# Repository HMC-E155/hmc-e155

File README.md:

# E155: Microprocessor-based Systems at Harvey Mudd College

This repository contains source code related to E155: Microprocessor-based Systems (MicroPs) at Harvey Mudd College.
See the [course website](https://hmc-e155.github.io/) for more details.

# Repository Structure

- [board](./board/) contains KiCad design files for the motherboard and breadboard adapter.
- [lab](./lab/) contains starter code for the labs as applicable.

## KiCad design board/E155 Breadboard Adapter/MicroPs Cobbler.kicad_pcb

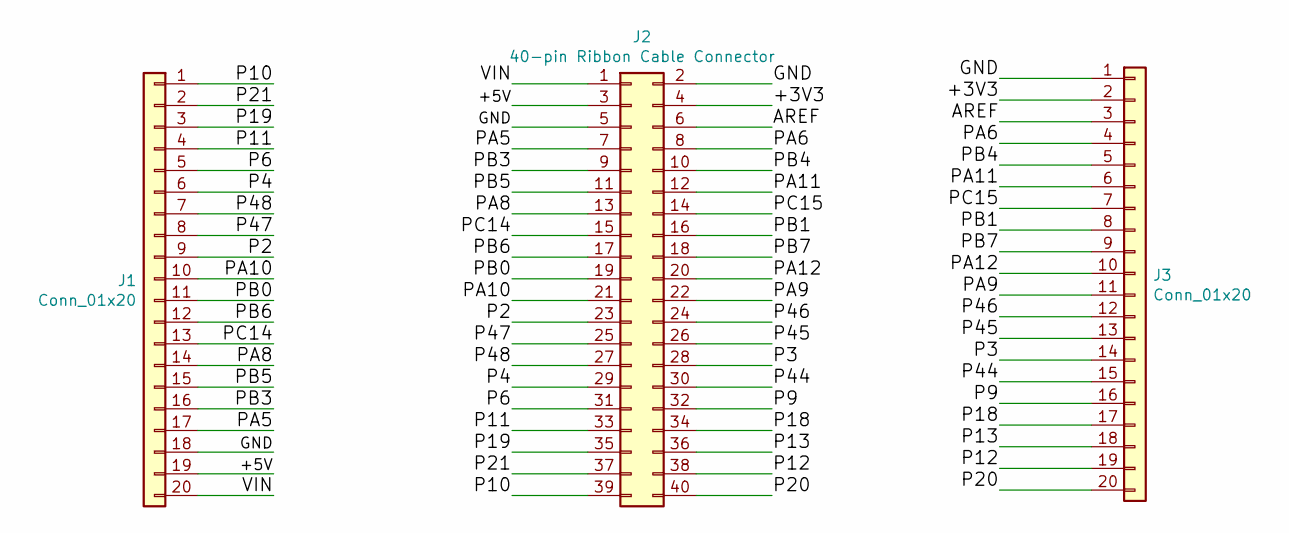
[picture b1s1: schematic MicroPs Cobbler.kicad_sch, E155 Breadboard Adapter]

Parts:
J1, J3: Conn_01x20; PinHeader_1x20_P2.54mm_Vertical
J2: 40-pin Ribbon Cable Connector; 2x20 Pin Header Keyed

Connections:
/+3V3: J2.4, J3.2
/+5V: J1.19, J2.3
/AREF: J2.6, J3.3
/GND: J1.18, J2.2, J2.5, J3.1
/P2: J1.9, J2.23
/P3: J2.28, J3.14
/P4: J1.6, J2.29
/P6: J1.5, J2.31
/P9: J2.32, J3.16
/P10: J1.1, J2.39
/P11: J1.4, J2.33
/P12: J2.38, J3.19
/P13: J2.36, J3.18
/P18: J2.34, J3.17
/P19: J1.3, J2.35
/P20: J2.40, J3.20
/P21: J1.2, J2.37
/P44: J2.30, J3.15
/P45: J2.26, J3.13
/P46: J2.24, J3.12
/P47: J1.8, J2.25
/P48: J1.7, J2.27
/PA5: J1.17, J2.7
/PA6: J2.8, J3.4
/PA8: J1.14, J2.13
/PA9: J2.22, J3.11
/PA10: J1.10, J2.21
/PA11: J2.12, J3.6
/PA12: J2.20, J3.10
/PB0: J1.11, J2.19
/PB1: J2.16, J3.8
/PB3: J1.16, J2.9
/PB4: J2.10, J3.5
/PB5: J1.15, J2.11
/PB6: J1.12, J2.17
/PB7: J2.18, J3.9
/PC14: J1.13, J2.15
/PC15: J2.14, J3.7
/VIN: J1.20, J2.1

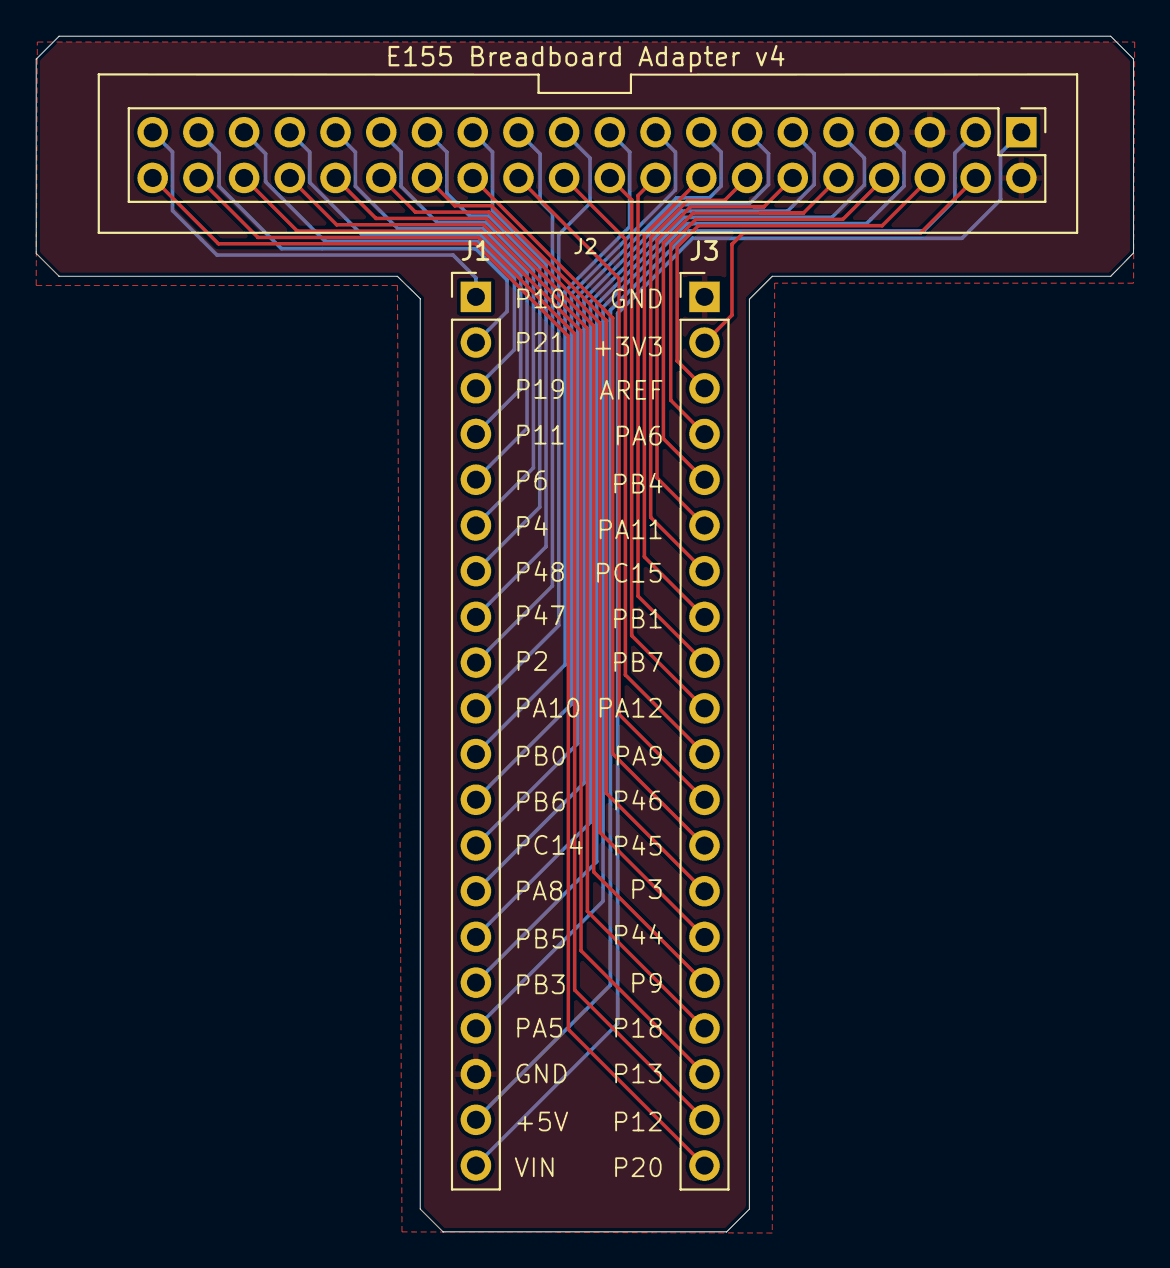
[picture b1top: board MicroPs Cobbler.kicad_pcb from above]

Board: 2 copper layers, 61.0 x 66.4 mm, 3 parts (0 on the bottom side), 39 nets.

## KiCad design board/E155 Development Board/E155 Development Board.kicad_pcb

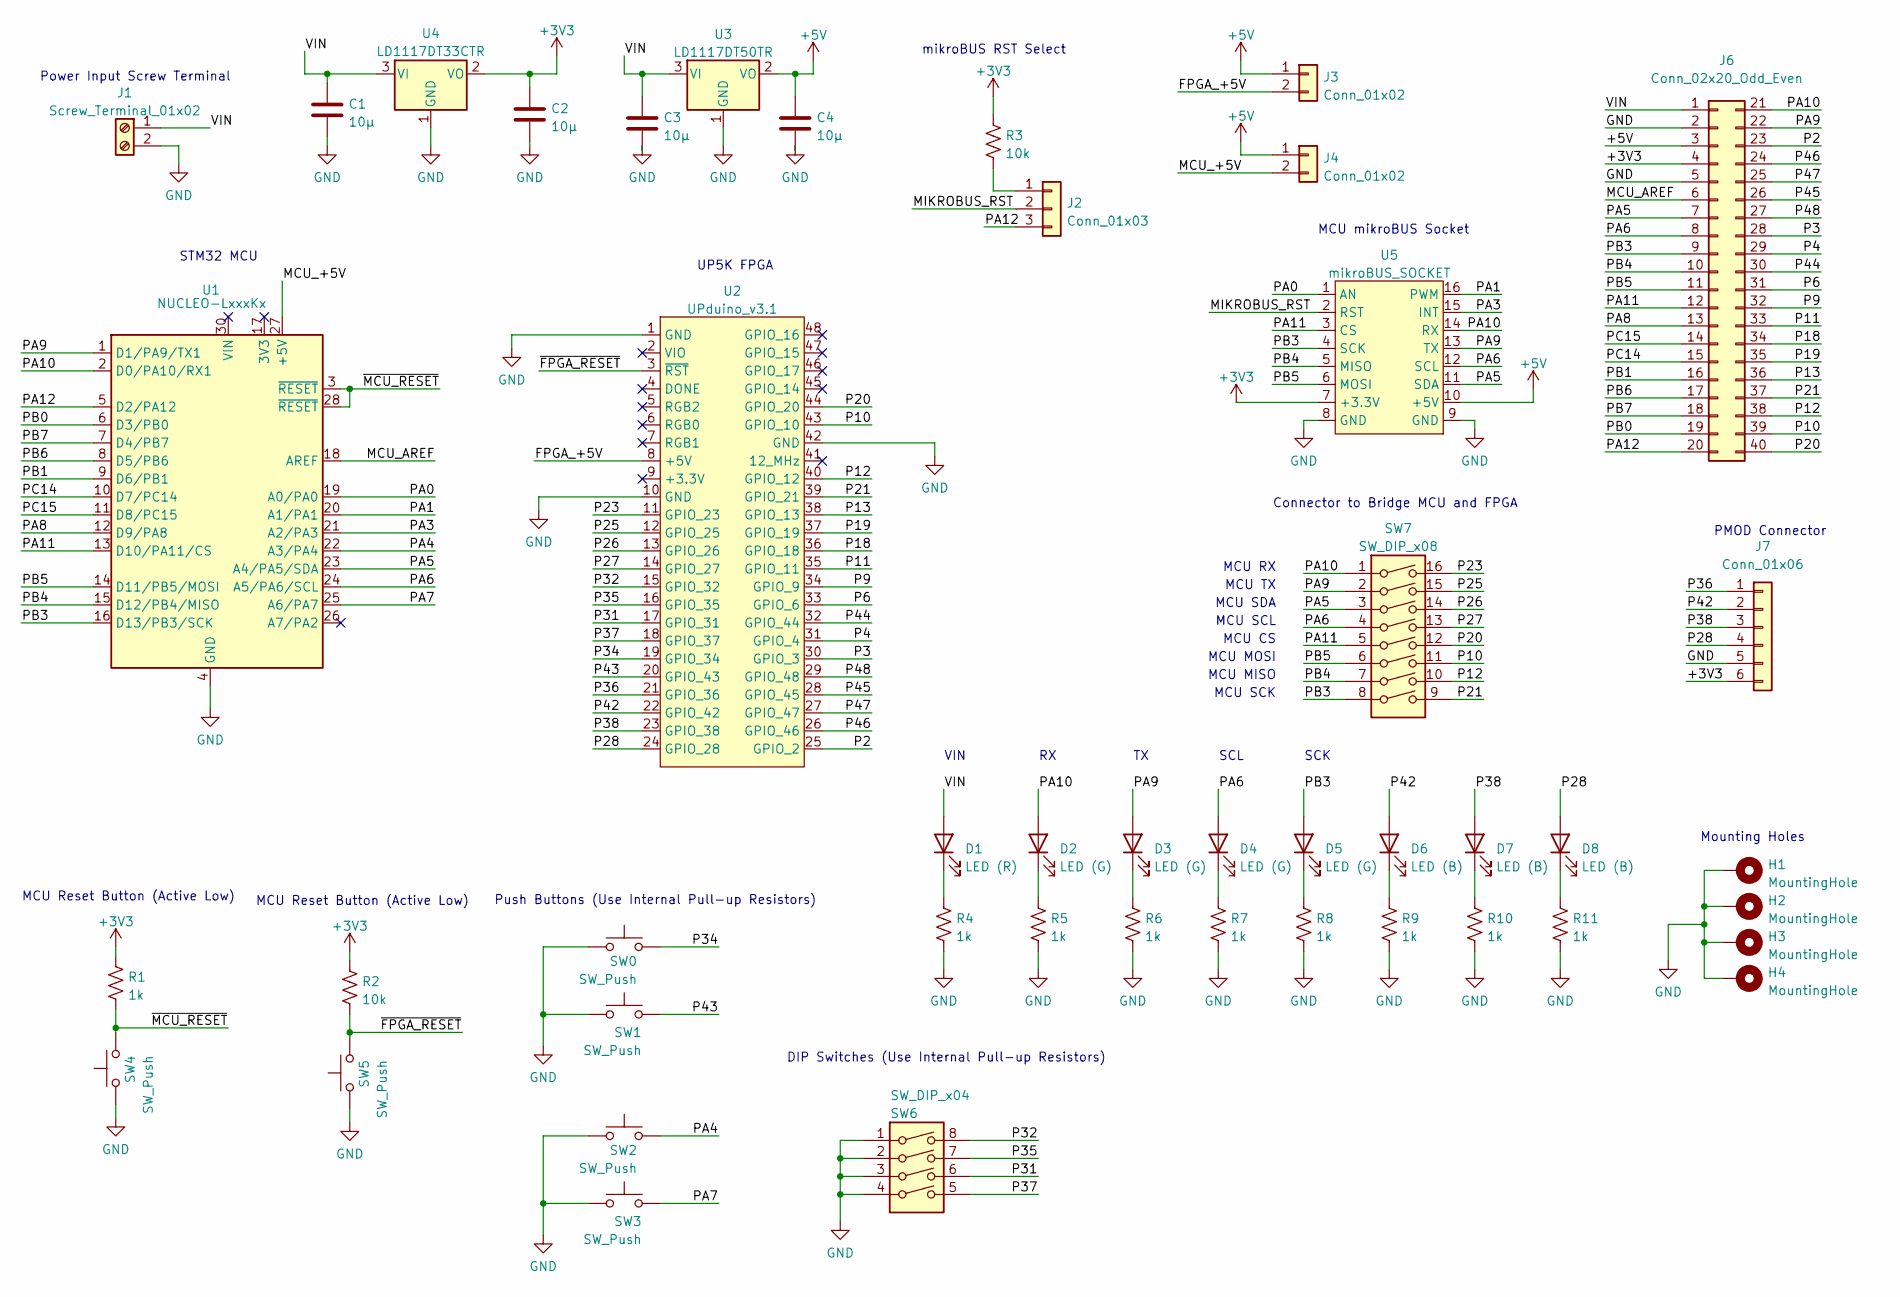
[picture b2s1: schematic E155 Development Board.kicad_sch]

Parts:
C1, C2, C3, C4: 10µ; C_0805_2012Metric_Pad1.18x1.45mm_HandSolder
D1: LED (R); LED_0805_2012Metric_Pad1.15x1.40mm_HandSolder
D2, D3, D4, D5: LED (G); LED_0805_2012Metric_Pad1.15x1.40mm_HandSolder
D6, D7, D8: LED (B); LED_0805_2012Metric_Pad1.15x1.40mm_HandSolder
H1, H2, H3, H4: MountingHole; MountingHole_4.3mm_M4_Pad
J1: Screw_Terminal_01x02; TerminalBlock_Phoenix_MKDS-1,5-2-5.08_1x02_P5.08mm_Horizont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
J2: Conn_01x03; PinHeader_1x03_P2.54mm_Vertical
J3, J4: Conn_01x02; PinHeader_1x02_P2.54mm_Vertical
J6: Conn_02x20_Odd_Even; 2x20 Pin Header Keyed
J7: Conn_01x06; PinSocket_1x06_P2.54mm_Vertical
R1, R4, R5, R6, R7, R8, R9, R10, R11: 1k; R_0805_2012Metric_Pad1.20x1.40mm_HandSolder
R2, R3: 10k; R_0805_2012Metric_Pad1.20x1.40mm_HandSolder
SW0, SW1, SW2, SW3, SW4, SW5: SW_Push; SW_PUSH_6mm_H4.3mm
SW6: SW_DIP_x04; SW_DIP_SPSTx04_Slide_6.7x11.72mm_W7.62mm_P2.54mm_LowProfile
SW7: SW_DIP_x08; SW_DIP_SPSTx08_Slide_6.7x21.88mm_W7.62mm_P2.54mm_LowProfile
U1: NUCLEO-LxxxKx; NUCLEO-32
U2: UPduino_v3.1
U3: LD1117DT50TR; TO-252-2
U4: LD1117DT33CTR; TO-252-2
U5: mikroBUS_SOCKET; MIKROBUS_HOST_CONN

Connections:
+3V3: C2.1, J6.4, J7.6, R1.1, R2.1, R3.1, U4.2 (VO), U5.7 (+3.3V)
+5V: C4.1, J3.1, J4.1, J6.3, U3.2 (VO), U5.10 (+5V)
/FPGA_+5V: J3.2, U2.8 (+5V)
/MCU_+5V: J4.2, U1.27 (+5V)
/MCU_AREF: J6.6, U1.18 (AREF)
/MIKROBUS_RST: J2.2, U5.2 (RST)
/P2: J6.23, U2.25 (GPIO_2)
/P3: J6.28, U2.30 (GPIO_3)
/P4: J6.29, U2.31 (GPIO_4)
/P6: J6.31, U2.33 (GPIO_6)
/P9: J6.32, U2.34 (GPIO_9)
/P10: J6.39, SW7.11, U2.43 (GPIO_10)
/P11: J6.33, U2.35 (GPIO_11)
/P12: J6.38, SW7.10, U2.40 (GPIO_12)
/P13: J6.36, U2.38 (GPIO_13)
/P18: J6.34, U2.36 (GPIO_18)
/P19: J6.35, U2.37 (GPIO_19)
/P20: J6.40, SW7.12, U2.44 (GPIO_20)
/P21: J6.37, SW7.9, U2.39 (GPIO_21)
/P23: SW7.16, U2.11 (GPIO_23)
/P25: SW7.15, U2.12 (GPIO_25)
/P26: SW7.14, U2.13 (GPIO_26)
/P27: SW7.13, U2.14 (GPIO_27)
/P28: D8.2 (A), J7.4, U2.24 (GPIO_28)
/P31: SW6.6, U2.17 (GPIO_31)
/P32: SW6.8, U2.15 (GPIO_32)
/P34: SW0.2, U2.19 (GPIO_34)
/P35: SW6.7, U2.16 (GPIO_35)
/P36: J7.1, U2.21 (GPIO_36)
/P37: SW6.5, U2.18 (GPIO_37)
/P38: D7.2 (A), J7.3, U2.23 (GPIO_38)
/P42: D6.2 (A), J7.2, U2.22 (GPIO_42)
/P43: SW1.2, U2.20 (GPIO_43)
/P44: J6.30, U2.32 (GPIO_44)
/P45: J6.26, U2.28 (GPIO_45)
/P46: J6.24, U2.26 (GPIO_46)
/P47: J6.25, U2.27 (GPIO_47)
/P48: J6.27, U2.29 (GPIO_48)
/PA0: U1.19 (A0/PA0), U5.1 (AN)
/PA1: U1.20 (A1/PA1), U5.16 (PWM)
/PA2: U1.26 (A7/PA2)
/PA3: U1.21 (A2/PA3), U5.15 (INT)
/PA4: SW2.2, U1.22 (A3/PA4)
/PA5: J6.7, SW7.3, U1.23 (A4/PA5/SDA), U5.11 (SDA)
/PA6: D4.2 (A), J6.8, SW7.4, U1.24 (A5/PA6/SCL), U5.12 (SCL)
/PA7: SW3.2, U1.25 (A6/PA7)
/PA8: J6.13, U1.12 (D9/PA8)
/PA9: D3.2 (A), J6.22, SW7.2, U1.1 (D1/PA9/TX1), U5.13 (TX)
/PA10: D2.2 (A), J6.21, SW7.1, U1.2 (D0/PA10/RX1), U5.14 (RX)
/PA11: J6.12, SW7.5, U1.13 (D10/PA11/CS), U5.3 (CS)
/PA12: J2.3, J6.20, U1.5 (D2/PA12)
/PB0: J6.19, U1.6 (D3/PB0)
/PB1: J6.16, U1.9 (D6/PB1)
/PB3: D5.2 (A), J6.9, SW7.8, U1.16 (D13/PB3/SCK), U5.4 (SCK)
/PB4: J6.10, SW7.7, U1.15 (D12/PB4/MISO), U5.5 (MISO)
/PB5: J6.11, SW7.6, U1.14 (D11/PB5/MOSI), U5.6 (MOSI)
/PB6: J6.17, U1.8 (D5/PB6)
/PB7: J6.18, U1.7 (D4/PB7)
/PC14: J6.15, U1.10 (D7/PC14)
/PC15: J6.14, U1.11 (D8/PC15)
/VIN: C1.1, C3.1, D1.2 (A), J1.1, J6.1, U3.3 (VI), U4.3 (VI)
/~FPGA_RESET: R2.2, SW5.2, U2.3 (~RST)
/~MCU_RESET: R1.2, SW4.2, U1.3 (~RESET), U1.28 (~RESET)
GND: C1.2, C2.2, C3.2, C4.2, H1.1, H2.1, H3.1, H4.1, J1.2, J6.2, J6.5, J7.5, R4.2, R5.2, R6.2, R7.2, R8.2, R9.2, R10.2, R11.2, SW0.1, SW1.1, SW2.1, SW3.1, SW4.1, SW5.1, SW6.1, SW6.2, SW6.3, SW6.4, U1.4 (GND), U1.29 (GND), U2.1 (GND), U2.10 (GND), U2.42 (GND), U3.1 (GND), U4.1 (GND), U5.8 (GND), U5.9 (GND)
unnamed: D1.1 (K), R4.1
unnamed: D2.1 (K), R5.1
unnamed: D3.1 (K), R6.1
unnamed: D4.1 (K), R7.1
unnamed: D5.1 (K), R8.1
unnamed: D6.1 (K), R9.1
unnamed: D7.1 (K), R10.1
unnamed: D8.1 (K), R11.1
unnamed: J2.1, R3.2

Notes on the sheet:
MCU SCK
MCU Reset Button (Active Low)
MCU SDA
STM32 MCU
MCU MOSI
mikroBUS RST Select
SCK
MCU TX
UP5K FPGA
Push Buttons (Use Internal Pull-up Resistors)
Mounting Holes
MCU RX
PMOD Connector
Power Input Screw Terminal
MCU CS
DIP Switches (Use Internal Pull-up Resistors)
MCU MISO
MCU SCL
VIN
SCL
Connector to Bridge MCU and FPGA
MCU mikroBUS Socket

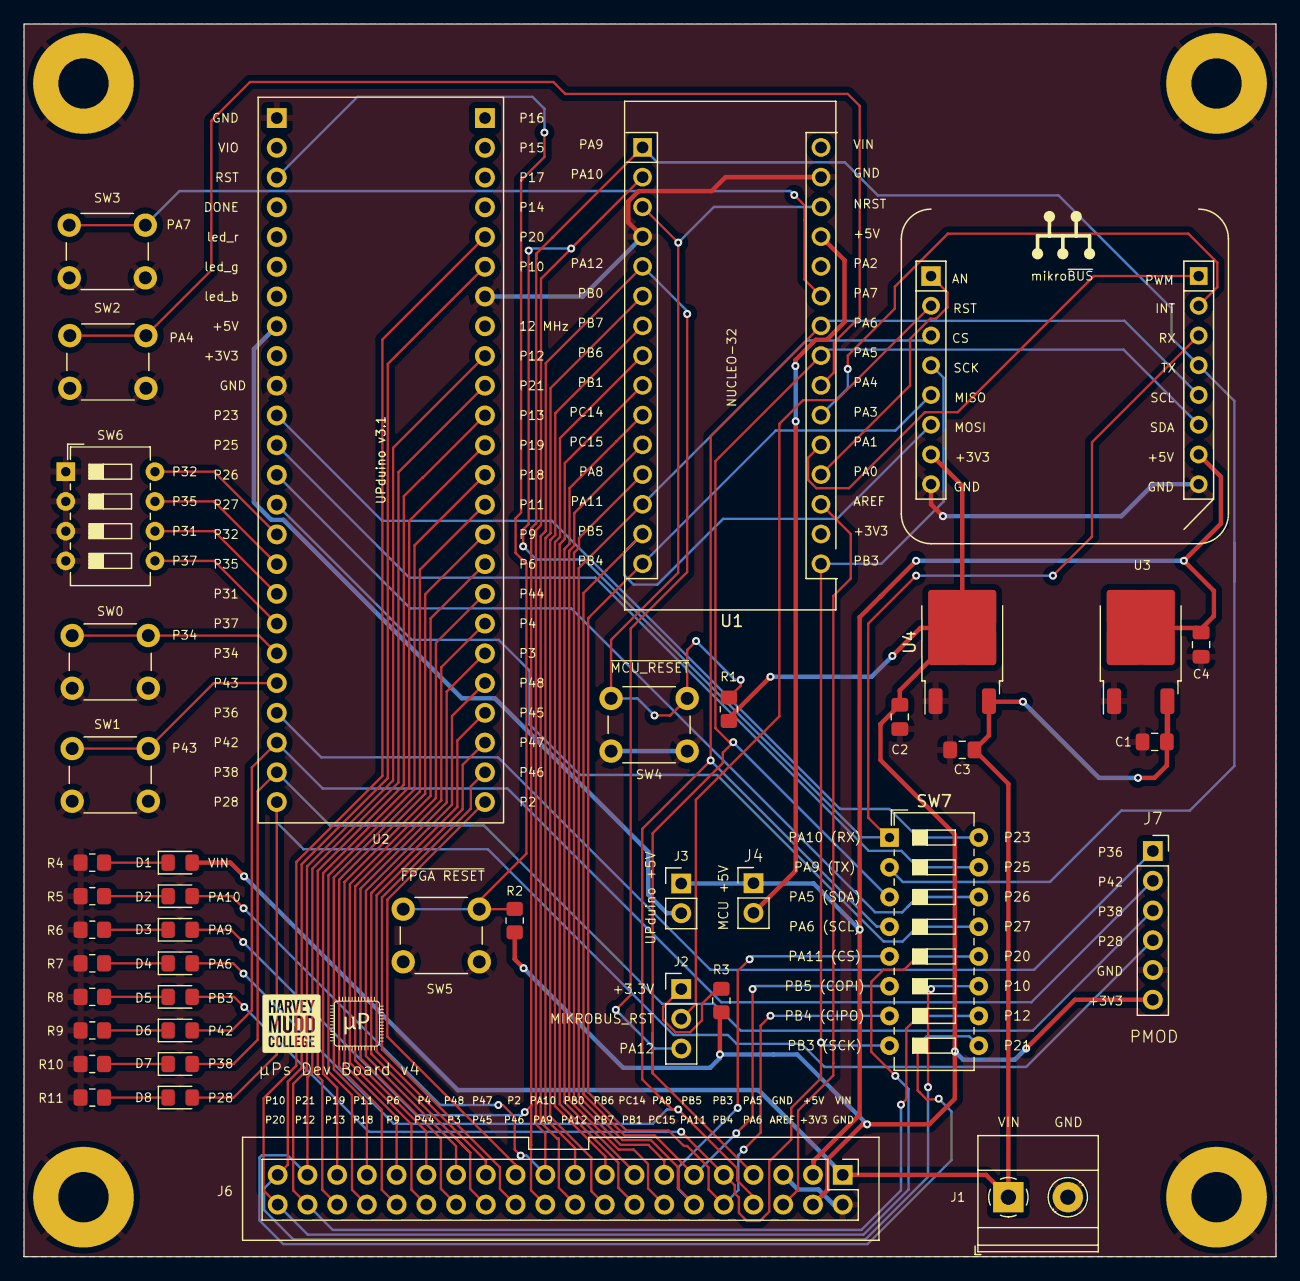
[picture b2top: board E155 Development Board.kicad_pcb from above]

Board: 2 copper layers, 106.9 x 105.3 mm, 46 parts (0 on the bottom side), 72 nets.

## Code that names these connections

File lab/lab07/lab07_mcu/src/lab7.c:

/**
    Main: Contains main function for AES SPI communication with FPGA.
    Sends the plaintext and key over SPI to the FPGA and then receives back
    the cyphertext. The cyphertext is then compared against the solution
    listed in Appendix A of the AES FIPS 197 standard.
    @file lab7.c
    @author Josh Brake
    @version 1.0 7/13/2021
*/
#include <stdio.h>
#include <stm32l432xx.h>
#include "STM32L432KC.h"

////////////////////////////////////////////////
// Constants
////////////////////////////////////////////////

#define MCK_FREQ 100000

// Test Case from Appendix A.1, B
char key[16] = {0x2B, 0x7E, 0x15, 0x16, 0x28, 0xAE, 0xD2, 0xA6,
                0xAB, 0xF7, 0x15, 0x88, 0x09, 0xCF, 0x4F, 0x3C};

char plaintext[16] = {0x32, 0x43, 0xF6, 0xA8, 0x88, 0x5A, 0x30, 0x8D,
                      0x31, 0x31, 0x98, 0xA2, 0xE0, 0x37, 0x07, 0x34};

char ct[16] = {0x39, 0x25, 0x84, 0x1D, 0x02, 0xDC, 0x09, 0xFB,
               0xDC, 0x11, 0x85, 0x97, 0x19, 0x6A, 0x0B, 0x32};

/* 
// Another test case from Appendix C.1

char key[16] = {0x00, 0x01, 0x02, 0x03, 0x04, 0x05, 0x06, 0x07,
                0x08, 0x09, 0x0A, 0x0B, 0x0C, 0x0D, 0x0E, 0x0F};

char plaintext[16] = {0x00, 0x11, 0x22, 0x33, 0x44, 0x55, 0x66, 0x77,
                      0x88, 0x99, 0xAA, 0xBB, 0xCC, 0xDD, 0xEE, 0xFF};

char ct[16] = {0x69, 0xC4, 0xE0, 0xD8, 0x6A, 0x7B, 0x04, 0x30,
               0xD8, 0xCD, 0xB7, 0x80, 0x70, 0xB4, 0xC5, 0x5A};
*/

////////////////////////////////////////////////
// Function Prototypes
////////////////////////////////////////////////

void encrypt(char*, char*, char*);
void checkAnswer(char*, char*, char*);

////////////////////////////////////////////////
// Main
////////////////////////////////////////////////

int main(void) {
  char cyphertext[16];

  // Configure flash latency and set clock to run at 84 MHz

  // Enable GPIOA clock
  RCC->AHB2ENR |= (RCC_AHB2ENR_GPIOAEN | RCC_AHB2ENR_GPIOBEN | RCC_AHB2ENR_GPIOCEN);

  // "clock divide" = master clock frequency / desired baud rate
  // the phase for the SPI clock is 1 and the polarity is 0
  initSPI(1, 0, 0);


  // Load and done pins
  pinMode(PA5, GPIO_OUTPUT);  // LOAD
  pinMode(PA6, GPIO_INPUT);   // DONE
  
  // debugging LEDs
  pinMode(PA9, GPIO_OUTPUT);
  pinMode(PA10, GPIO_OUTPUT);
  digitalWrite(PA9, 0);
  digitalWrite(PA10, 0);

  // Artificial chip select signal to allow 8-bit CE-based SPI decoding on the logic analyzers.
  pinMode(PA11, GPIO_OUTPUT);
  digitalWrite(PA11, 1);


  // hardware accelerated encryption
  encrypt(key, plaintext, cyphertext);
  checkAnswer(key, plaintext, cyphertext);
}

////////////////////////////////////////////////
// Functions
////////////////////////////////////////////////

void checkAnswer(char * key, char * plaintext, char * cyphertext) {
  // Compare Strings:
  char correct = 1;
  for(int i = 0; i < 16; i++) {
    volatile int k = cyphertext[i] - ct[i];
    
    if(k != 0) {
      correct = 0;
    }
  }

  if(correct) {
    digitalWrite(PA9, 1); // Success!
  } else {
    digitalWrite(PA10, 1);    // Bummer.  Test failed.
  }
  }

void encrypt(char * key, char * plaintext, char * cyphertext) {
  int i;

  // Write LOAD high
  digitalWrite(PA5, 1);

  // Send plaintext
  for(i = 0; i < 16; i++) {
    digitalWrite(PA11, 1); // Arificial CE high
    spiSendReceive(plaintext[i]);
    digitalWrite(PA11, 0); // Arificial CE low
  }

  // Send the key
  for(i = 0; i < 16; i++) {
    digitalWrite(PA11, 1); // Arificial CE high
    spiSendReceive(key[i]);
    digitalWrite(PA11, 0); // Arificial CE low
  }

  while(SPI1->SR & SPI_SR_BSY); // Confirm all SPI transactions are completed
  digitalWrite(PA5, 0); // Write LOAD low

  // Wait for DONE signal to be asserted by FPGA signifying that the data is ready to be read out.
  while(!digitalRead(PA6));

  for(i = 0; i < 16; i++) {
    digitalWrite(PA11, 1); // Arificial CE high
    cyphertext[i] = spiSendReceive(0);  
    digitalWrite(PA11, 0); // Arificial CE low
  }
}

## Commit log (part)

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2023-04-25 Removed .DS_Store
2023-08-18 Updated .gitignore to ignore Quarto files
2023-08-18 Removed .quarto files
2023-08-18 Got rid of .DS_Store
2023-08-18 Removed lecture demo
2023-08-23 Added new BOM XLSX and HTML sheet.
2023-08-23 Added .gitignore
2023-08-23 Removed .DS_Store files.
2023-08-23 Added _site to .gitignore
2023-08-23 Added initial README
2023-08-30 Added lab1 files
2023-09-01 Added lab 1 source code.
2023-09-01 Removed old lab 1 code
2023-09-01 Added lab 4 starter source code
2023-09-01 Added lab 5 starter code
2023-09-01 Added lab 6 starter code
2023-09-01 Added lab 7 starter code
2023-09-04 FA23 board files.
2023-09-26 Added blink demo source code
2023-09-26 Added clock configuration source code
2023-09-26 Added readmes for blink and clock config demos
2023-09-28 Added timer lecture example.
2023-09-28 Added infinite loop at the bottom to stay in after sorting.
2023-10-06 Added UART example
2023-10-06 Added ESP8266 demo code.
2023-10-06 Moved demos to new folder
2023-10-09 Removed SPI libraries (Lab 6 solution) from the webserver demo.
2023-10-10 Added ESP8266 webserver code.
2023-10-31 Added interrupts demo code.
2023-11-02 add chip select/enable for decoding SPI transaction on logic analyzer
2023-11-02 Update button pin to PA4
2023-11-06 Removed web files from public repository.
2023-11-06 Updated README to match the new changes.
2023-11-06 Updated formatting of list in README.
2023-11-06 Added Readme for Lab 1
2023-11-30 Added FreeRTOS example
2023-11-30 Embedded Loom tutorial video.
2023-11-30 Updated README to avoid video embed.
2023-11-30 Reduced size of heap in FreeRTOSConfig.h to avoid error.
2023-11-30 Fixed errors related to missing config options.
2024-02-29 Added initial version of the course website
2024-02-29 Initializing gh-pages branch
2024-02-29 Built site for gh-pages
2024-02-29 Updated web files for public site
2024-02-29 Updated the website to remove the reference to a specific year
2024-07-03 Remove web subfolder from public E155 repo
2024-07-11 Updated link to course website
2024-07-23 Board updates for FA24
    Removed specific text on the board which references a year and changed it to a version number. Also updated the libraries and KiCad files to resolve design check issues.
2024-07-23 Updated HTML BOM
2024-08-27 Updated .gitignore for KiCad
2024-09-23 Updated Lab 4
    Removed starter code to the assembly lab and replaced with the code from old lab 5 on digital audio.
2024-09-23 Updated Lab 4 (#5)
    Removed starter code to the assembly lab and replaced with the code from old lab 5 on digital audio.
2024-09-23 Revert "Updated Lab 4 (#5)"
    This reverts commit c5787f6b9614f6f07571d5bf1df980f82c137749.
2024-09-23 Updated Lab 4 (#6)
    Removed starter code to the assembly lab and replaced with the code from old lab 5 on digital audio.
2024-10-23 Remove all demos. Now converted to single tutorial repos.
2024-10-23 Updated README to remove link to demos folder
2024-10-23 Remove all demos. Now converted to single tutorial repos. (#7)
    * Remove all demos. Now converted to single tutorial repos.
    * Updated README to remove link to demos folder
2024-10-23 add chip select/enable for decoding SPI transaction on logic analyzer (#3)
